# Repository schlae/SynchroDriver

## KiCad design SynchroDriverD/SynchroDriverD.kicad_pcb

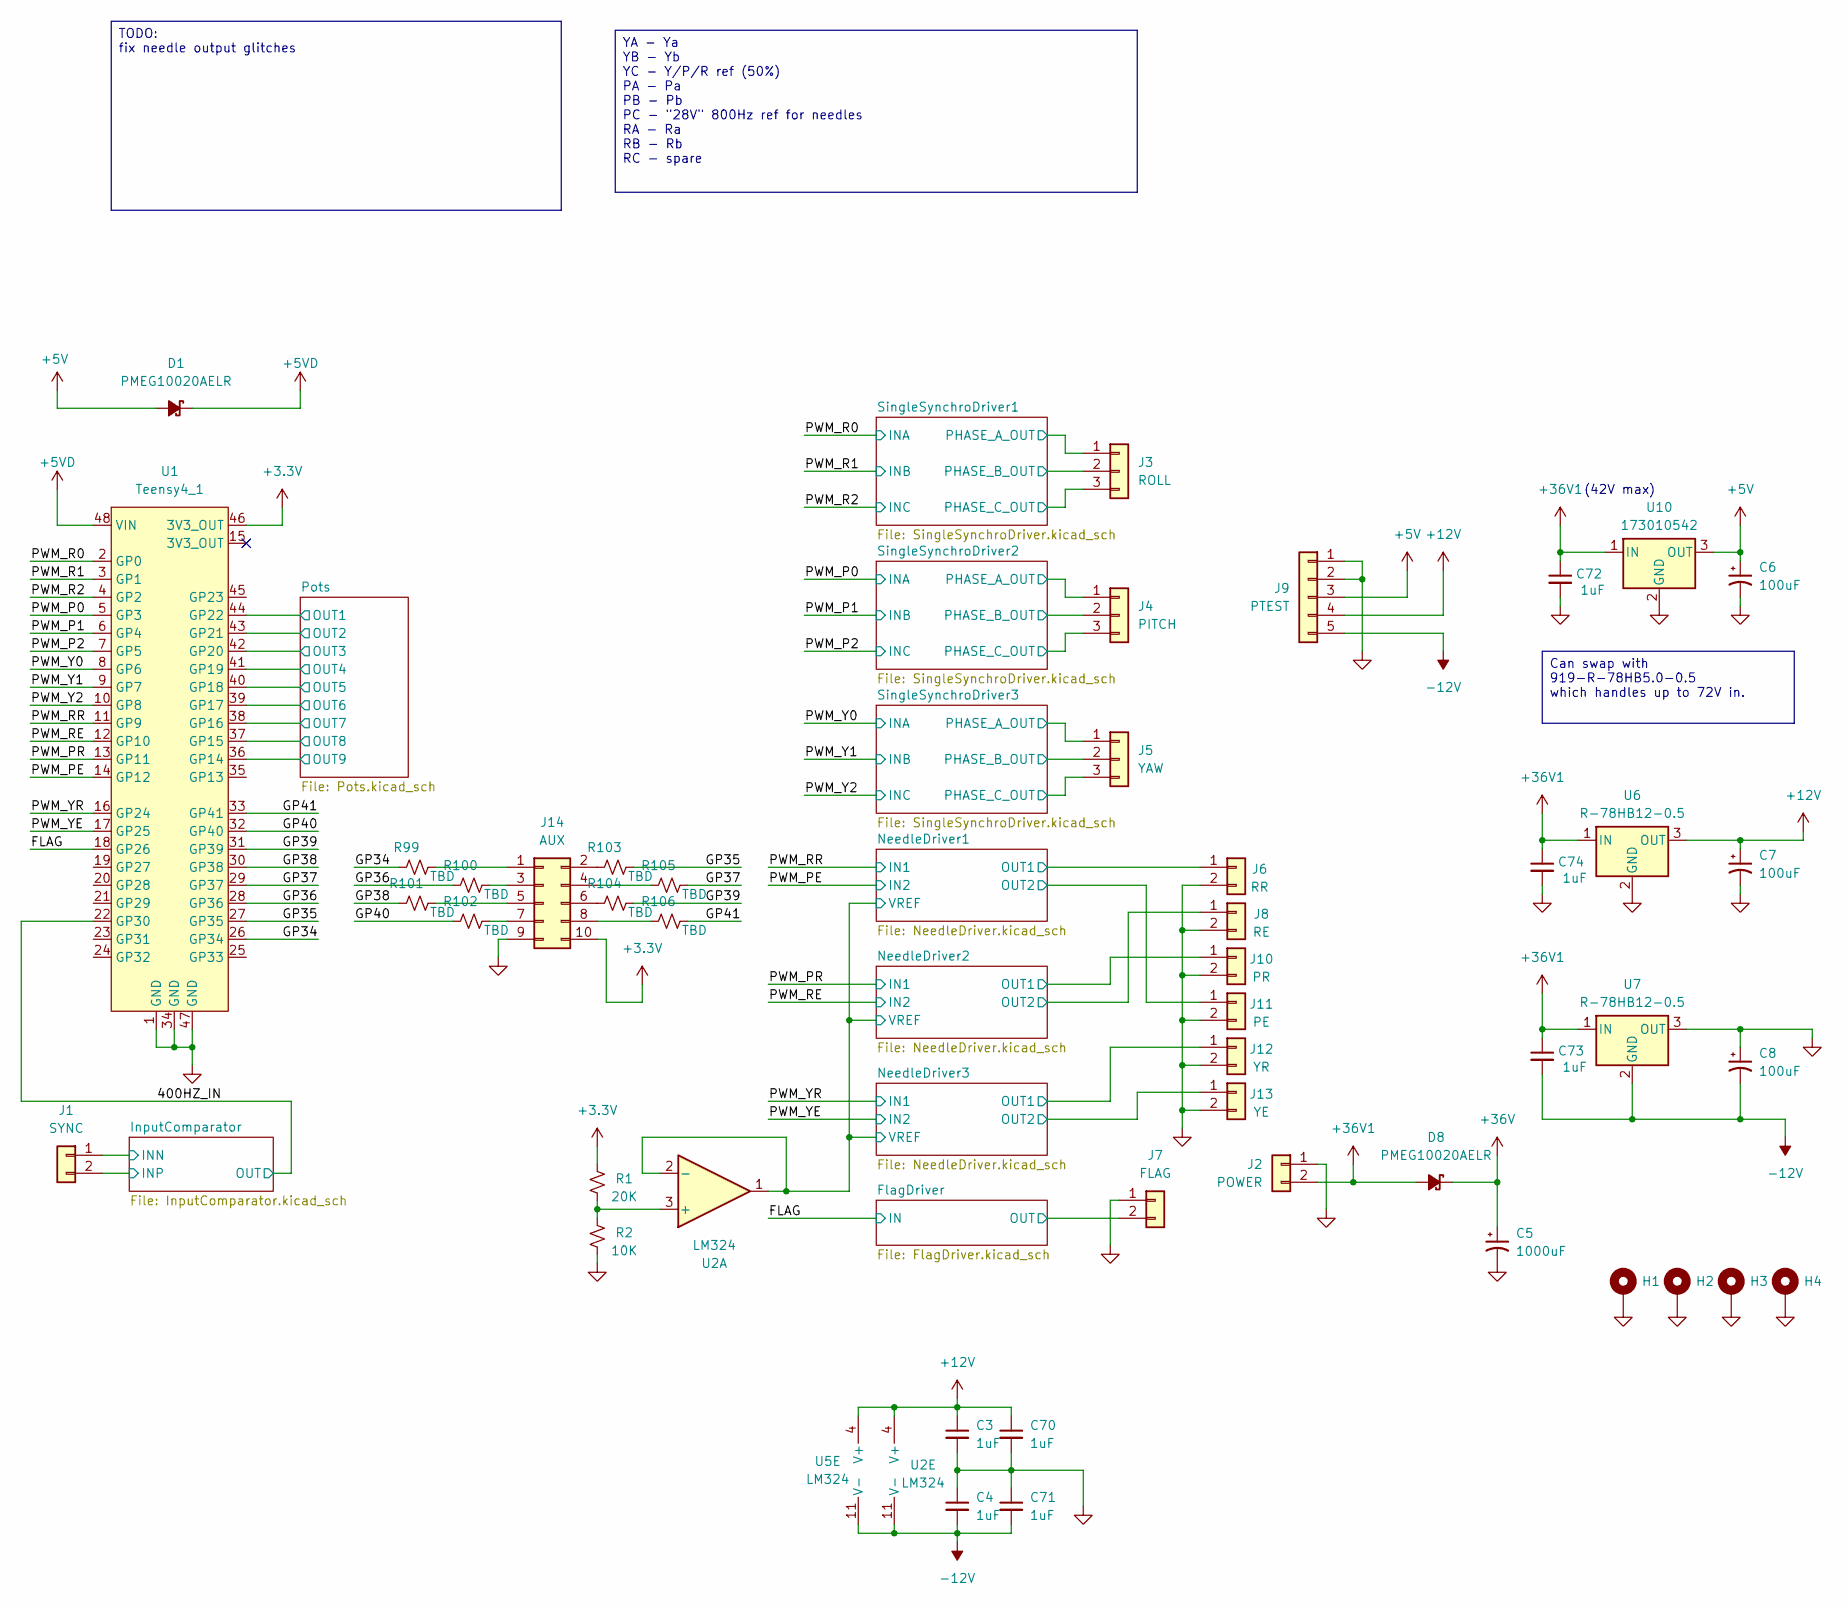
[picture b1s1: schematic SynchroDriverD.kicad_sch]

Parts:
C3, C4, C70, C71: 1uF; CAPC2012X55
C5: 1000uF; CAPAE500P1000X1500
C6, C7, C8: 100uF; CAPAE350P800X700
C72, C73, C74: 1uF; C_1206_3216Metric; MPN CL31A106KBHNNNE
D1, D8: PMEG10020AELR; SOD3716X117; Mouser 771-PMEG10020AELRX
H1, H2, H3, H4: MountingHole_Pad; MountingHole_3.2mm_M3_DIN965_Pad
J1: SYNC; PinHeader_1x02_P2.54mm_Vertical
J2: POWER; TE_826576-2_1x02_P3.96mm_Vertical
J3: ROLL; PinHeader_1x03_P2.54mm_Vertical
J4: PITCH; PinHeader_1x03_P2.54mm_Vertical
J5: YAW; PinHeader_1x03_P2.54mm_Vertical
J6: RR; PinHeader_1x02_P2.54mm_Vertical
J7: FLAG; PinHeader_1x02_P2.54mm_Vertical
J8: RE; PinHeader_1x02_P2.54mm_Vertical
J9: PTEST; TE_826576-5_1x05_P3.96mm_Vertical
J10: PR; PinHeader_1x02_P2.54mm_Vertical
J11: PE; PinHeader_1x02_P2.54mm_Vertical
J12: YR; PinHeader_1x02_P2.54mm_Vertical
J13: YE; PinHeader_1x02_P2.54mm_Vertical
J14: AUX; PinHeader_2x05_P2.54mm_Vertical
R1: 20K; RESC1608X55
R2: 10K; RESC1608X55
R99, R100, R101, R102, R103, R104, R105, R106: TBD; RESC1608X55
U1: Teensy4_1; DIP-48_W15.24mm_Socket
U2, U5: LM324; SOP127P620X175-14; Mouser 863-LM324DR2G
U6, U7: R-78HB12-0.5; DCDC_3PIN_GENERIC_SHIFTED; Mouser 919-R-78HB12-0.5
U10: 173010542; DCDC_3PIN_GENERIC; Mouser 710-173010542

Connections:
+3.3V: J14.10, R1.2, U1.46 (3V3_OUT); also elsewhere on the board
+5V: C6.1, D1.2 (A), J9.3, U10.3 (OUT); also elsewhere on the board
+5VD: D1.1 (K), U1.48 (VIN)
+12V: C3.1, C7.1, C70.1, J9.4, U2.4 (V+), U5.4 (V+), U6.3 (OUT); also elsewhere on the board
+36V: C5.1, D8.1 (K); also elsewhere on the board
+36V1: C72.1, C73.1, C74.1, D8.2 (A), J2.2, U6.1 (IN), U7.1 (IN), U10.1 (IN); also elsewhere on the board
-12V: C4.2, C8.2, C71.2, C73.2, J9.5, U2.11 (V-), U5.11 (V-), U7.2 (GND); also elsewhere on the board
/400HZ_IN: U1.22 (GP30); also elsewhere on the board
/FLAG: U1.18 (GP26); also elsewhere on the board
/FlagDriver/OUT: J7.2; also elsewhere on the board
/GP34: R99.2, U1.26 (GP34)
/GP35: R103.1, U1.27 (GP35)
/GP36: R100.2, U1.28 (GP36)
/GP37: R105.1, U1.29 (GP37)
/GP38: R101.2, U1.30 (GP38)
/GP39: R104.1, U1.31 (GP39)
/GP40: R102.2, U1.32 (GP40)
/GP41: R106.1, U1.33 (GP41)
/InputComparator/INN: J1.1; also elsewhere on the board
/InputComparator/INP: J1.2; also elsewhere on the board
/NeedleDriver1/OUT1: J6.1; also elsewhere on the board
/NeedleDriver1/OUT2: J11.1; also elsewhere on the board
/NeedleDriver1/VREF: U2.1, U2.2 (-), U2.10 (+), U2.12 (+), U5.10 (+), U5.12 (+); also elsewhere on the board
/NeedleDriver2/OUT1: J10.1; also elsewhere on the board
/NeedleDriver2/OUT2: J8.1; also elsewhere on the board
/NeedleDriver3/OUT1: J12.1; also elsewhere on the board
/NeedleDriver3/OUT2: J13.1; also elsewhere on the board
/PWM_P0: U1.5 (GP3); also elsewhere on the board
/PWM_P1: U1.6 (GP4); also elsewhere on the board
/PWM_P2: U1.7 (GP5); also elsewhere on the board
/PWM_PE: U1.14 (GP12); also elsewhere on the board
/PWM_PR: U1.13 (GP11); also elsewhere on the board
/PWM_R0: U1.2 (GP0); also elsewhere on the board
/PWM_R1: U1.3 (GP1); also elsewhere on the board
/PWM_R2: U1.4 (GP2); also elsewhere on the board
/PWM_RE: U1.12 (GP10); also elsewhere on the board
/PWM_RR: U1.11 (GP9); also elsewhere on the board
/PWM_Y0: U1.8 (GP6); also elsewhere on the board
/PWM_Y1: U1.9 (GP7); also elsewhere on the board
/PWM_Y2: U1.10 (GP8); also elsewhere on the board
/PWM_YE: U1.17 (GP25); also elsewhere on the board
/PWM_YR: U1.16 (GP24); also elsewhere on the board
/Pots/OUT1: U1.44 (GP22); also elsewhere on the board
/Pots/OUT2: U1.43 (GP21); also elsewhere on the board
/Pots/OUT3: U1.42 (GP20); also elsewhere on the board
/Pots/OUT4: U1.41 (GP19); also elsewhere on the board
/Pots/OUT5: U1.40 (GP18); also elsewhere on the board
/Pots/OUT6: U1.39 (GP17); also elsewhere on the board
/Pots/OUT7: U1.38 (GP16); also elsewhere on the board
/Pots/OUT8: U1.37 (GP15); also elsewhere on the board
/Pots/OUT9: U1.36 (GP14); also elsewhere on the board
/SingleSynchroDriver1/PHASE_A_OUT: J3.1; also elsewhere on the board
/SingleSynchroDriver1/PHASE_B_OUT: J3.2; also elsewhere on the board
/SingleSynchroDriver1/PHASE_C_OUT: J3.3; also elsewhere on the board
/SingleSynchroDriver2/PHASE_A_OUT: J4.1; also elsewhere on the board
/SingleSynchroDriver2/PHASE_B_OUT: J4.2; also elsewhere on the board
/SingleSynchroDriver2/PHASE_C_OUT: J4.3; also elsewhere on the board
/SingleSynchroDriver3/PHASE_A_OUT: J5.1; also elsewhere on the board
/SingleSynchroDriver3/PHASE_B_OUT: J5.2; also elsewhere on the board
/SingleSynchroDriver3/PHASE_C_OUT: J5.3; also elsewhere on the board
GND: C3.2, C4.1, C5.2, C6.2, C7.2, C8.1, C70.2, C71.1, C72.2, C74.2, H1.1, H2.1, H3.1, H4.1, J2.1, J6.2, J7.1, J8.2, J9.1, J9.2, J10.2, J11.2, J12.2, J13.2, J14.9, R2.1, U1.1 (GND), U1.34 (GND), U1.47 (GND), U6.2 (GND), U7.3 (OUT), U10.2 (GND); also elsewhere on the board
unnamed 77: U5.8; also elsewhere on the board
unnamed 78: U5.14; also elsewhere on the board
unnamed 81: U2.14; also elsewhere on the board
unnamed 82: U2.8; also elsewhere on the board
unnamed: J14.1, R99.1
unnamed: J14.2, R103.2
unnamed: J14.3, R100.1
unnamed: J14.4, R105.2
unnamed: J14.5, R101.1
unnamed: J14.6, R104.2
unnamed: J14.7, R102.1
unnamed: J14.8, R106.2
unnamed: R1.1, R2.2, U2.3 (+)
unnamed 140: U2.9 (-); also elsewhere on the board
unnamed 141: U2.13 (-); also elsewhere on the board
unnamed 144: U5.9 (-); also elsewhere on the board
unnamed 145: U5.13 (-); also elsewhere on the board

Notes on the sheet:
(42V max)
Can swap with 919-R-78HB5.0-0.5 which handles up to 72V in.
YA - Ya YB - Yb YC - Y/P/R ref (50%) PA - Pa PB - Pb PC - "28V" 800Hz ref for needles RA - Ra RB - Rb RC - spare
TODO: fix needle output glitches

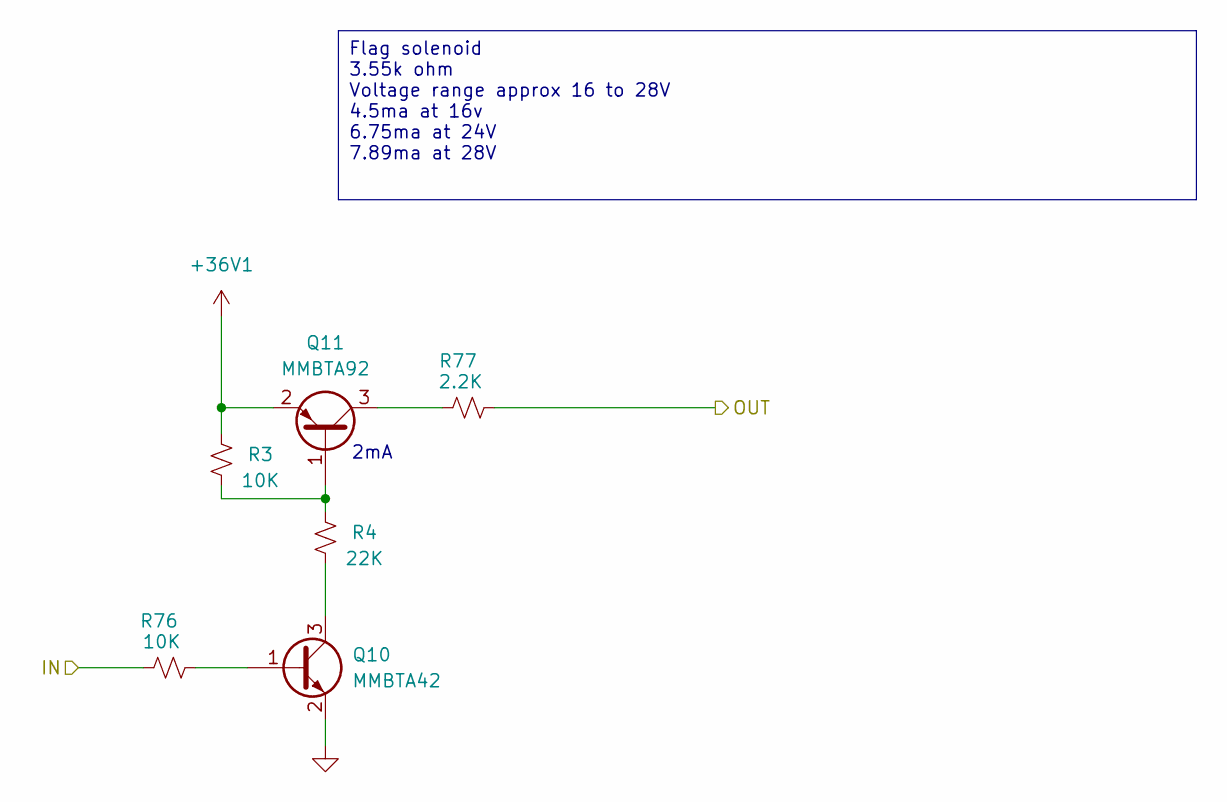
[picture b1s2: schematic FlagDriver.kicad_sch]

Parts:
Q10: MMBTA42; SOT-23; Mouser 637-MMBTA42
Q11: MMBTA92; SOT-23; Mouser 637-MMBTA92
R3, R76: 10K; R_0603_1608Metric
R4: 22K; R_0603_1608Metric
R77: 2.2K; R_0603_1608Metric

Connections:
+36V1: Q11.2 (E), R3.2; also elsewhere on the board
/FLAG: R76.2; also elsewhere on the board
/FlagDriver/OUT: R77.1; also elsewhere on the board
GND: Q10.2 (E); also elsewhere on the board
unnamed: Q10.1 (B), R76.1
unnamed: Q10.3 (C), R4.1
unnamed: Q11.1 (B), R3.1, R4.2
unnamed: Q11.3 (C), R77.2

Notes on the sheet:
2mA
Flag solenoid 3.55k ohm Voltage range approx 16 to 28V 4.5ma at 16v 6.75ma at 24V 7.89ma at 28V

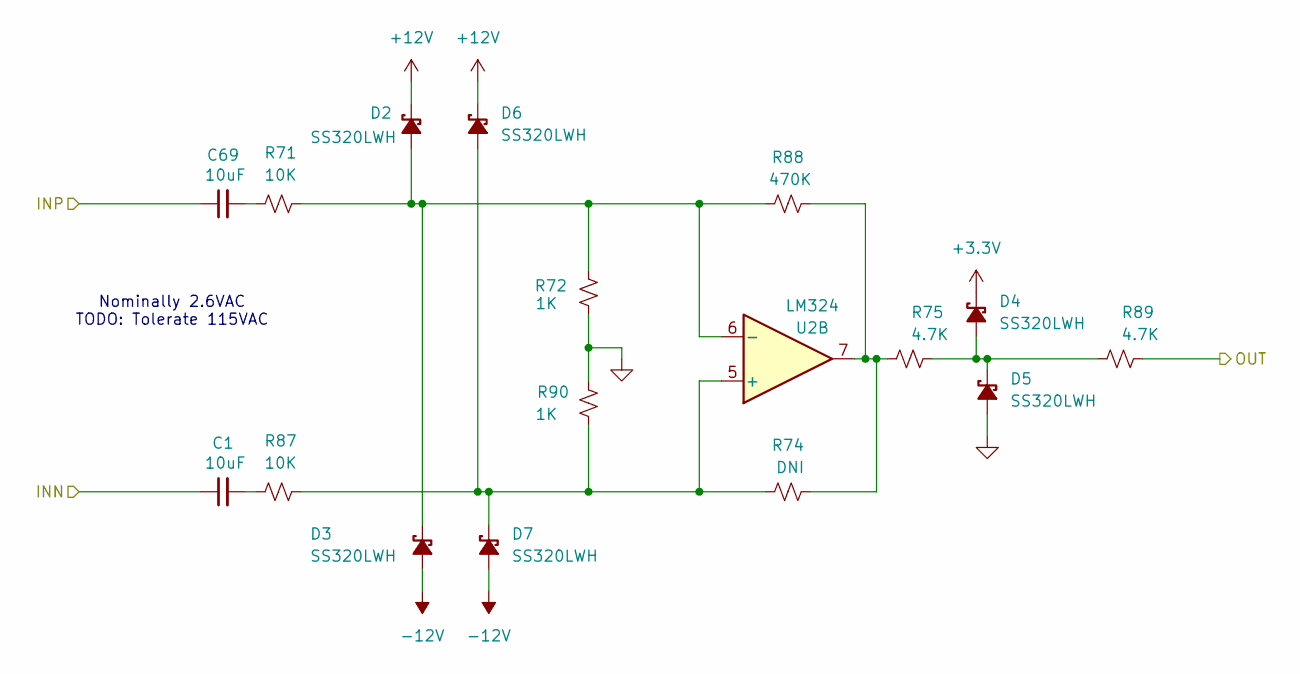
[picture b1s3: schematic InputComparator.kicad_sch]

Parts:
C1, C69: 10uF; C_1206_3216Metric; MPN CL31A106KBHNNNE; Mouser 187-CL31A106KBHNNNE
D2, D3, D4, D5, D6, D7: SS320LWH; SOD3716X117; Mouser 821-SS320LWH
R71, R87: 10K; RESC3216X70
R72, R90: 1K; RESC1608X55
R74: DNI; RESC1608X55
R75, R89: 4.7K; RESC1608X55
R88: 470K; RESC1608X55
U2: LM324; SOP127P620X175-14; Mouser 863-LM324DR2G

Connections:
+3.3V: D4.1 (K); also elsewhere on the board
+12V: D2.1 (K), D6.1 (K); also elsewhere on the board
-12V: D3.2 (A), D7.2 (A); also elsewhere on the board
/400HZ_IN: R89.1; also elsewhere on the board
/InputComparator/INN: C1.1; also elsewhere on the board
/InputComparator/INP: C69.1; also elsewhere on the board
/NeedleDriver1/VREF: U2.10 (+), U2.12 (+); also elsewhere on the board
GND: D5.2 (A), R72.2, R90.1; also elsewhere on the board
unnamed: C1.2, R87.1
unnamed 81: U2.14; also elsewhere on the board
unnamed 82: U2.8; also elsewhere on the board
unnamed: C69.2, R71.1
unnamed: D2.2 (A), D3.1 (K), R71.2, R72.1, R88.2, U2.6 (-)
unnamed: D4.2 (A), D5.1 (K), R75.1, R89.2
unnamed: D6.2 (A), D7.1 (K), R74.2, R87.2, R90.2, U2.5 (+)
unnamed: R74.1, R75.2, R88.1, U2.7
unnamed 140: U2.9 (-); also elsewhere on the board
unnamed 141: U2.13 (-); also elsewhere on the board

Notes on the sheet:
Nominally 2.6VAC TODO: Tolerate 115VAC

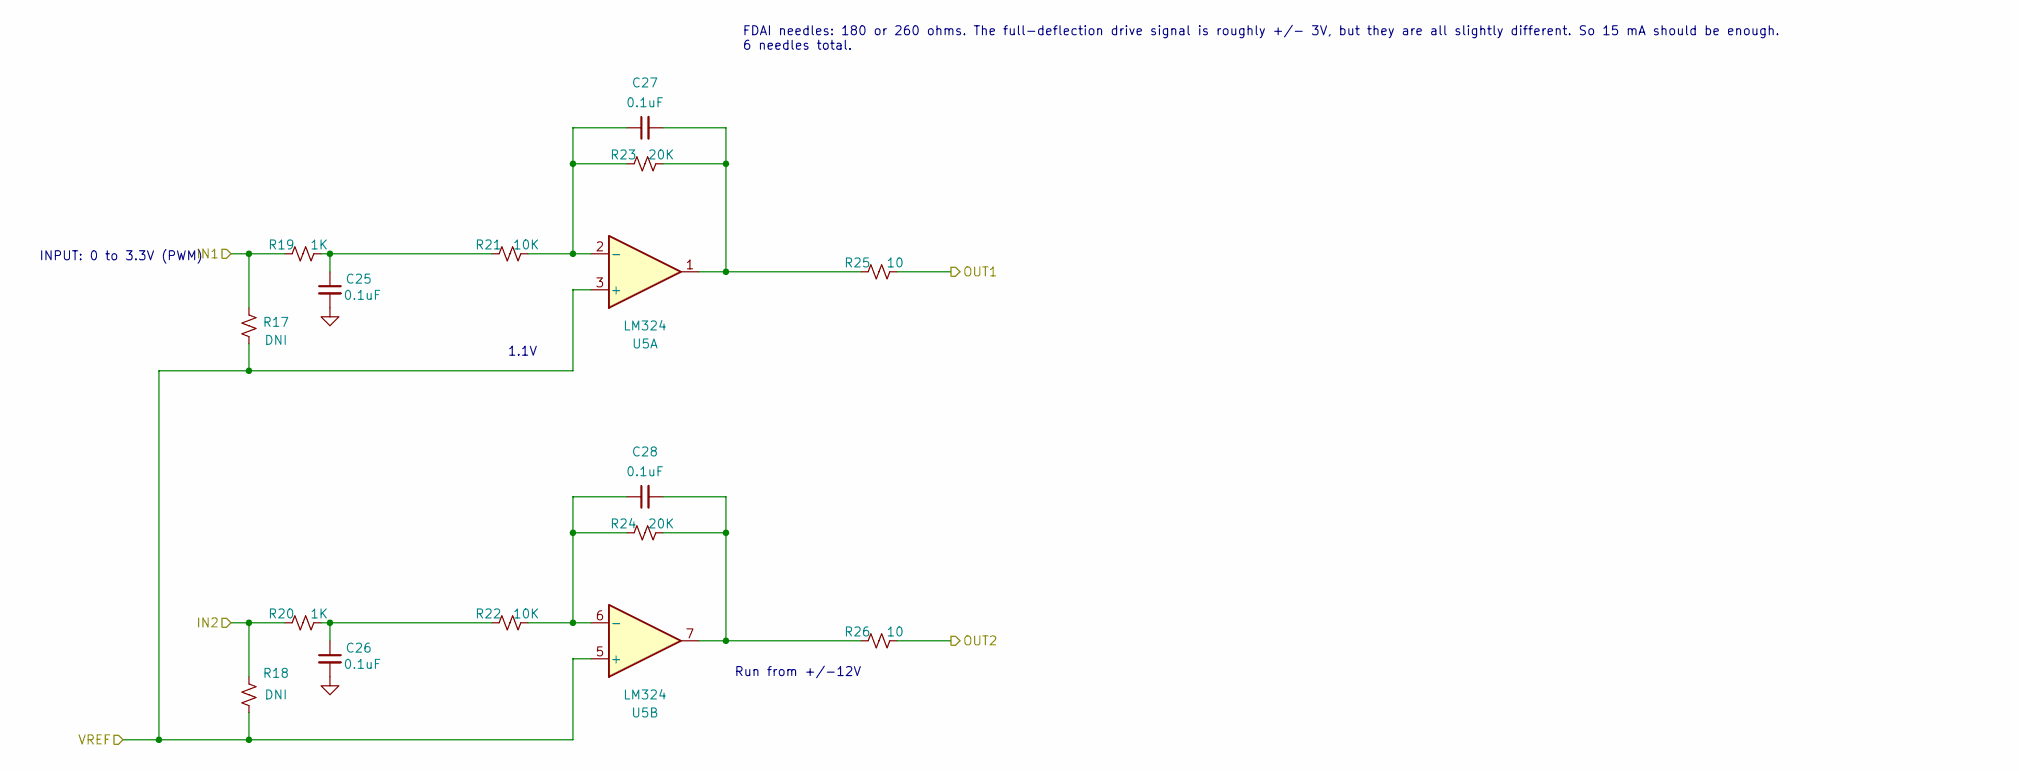
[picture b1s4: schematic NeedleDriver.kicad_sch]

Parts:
C25, C26, C27, C28: 0.1uF; CAPC1608X100
R17, R18: DNI; RESC1608X55
R19, R20: 1K; RESC1608X55
R21, R22: 10K; RESC1608X55
R23, R24: 20K; RESC1608X55
R25, R26: 10; RESC1608X55
U5: LM324; SOP127P620X175-14; Mouser 863-LM324DR2G

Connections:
/NeedleDriver1/OUT1: R25.2; also elsewhere on the board
/NeedleDriver1/OUT2: R26.2; also elsewhere on the board
/NeedleDriver1/VREF: R17.1, R18.1, U5.3 (+), U5.5 (+), U5.10 (+), U5.12 (+); also elsewhere on the board
/PWM_PE: R18.2, R20.1; also elsewhere on the board
/PWM_RR: R17.2, R19.1; also elsewhere on the board
GND: C25.2, C26.2; also elsewhere on the board
unnamed: C25.1, R19.2, R21.1
unnamed: C26.1, R20.2, R22.1
unnamed: C27.2, R23.2, R25.1, U5.1
unnamed: C28.2, R24.2, R26.1, U5.7
unnamed 77: U5.8; also elsewhere on the board
unnamed 78: U5.14; also elsewhere on the board
unnamed: C27.1, R21.2, R23.1, U5.2 (-)
unnamed: C28.1, R22.2, R24.1, U5.6 (-)
unnamed 144: U5.9 (-); also elsewhere on the board
unnamed 145: U5.13 (-); also elsewhere on the board

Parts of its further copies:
C29, C30, C31, C32, C33, C34, C35, C36: 0.1uF; CAPC1608X100
R27, R28, R37, R38: DNI; RESC1608X55
R29, R30, R39, R40: 1K; RESC1608X55
R31, R32, R41, R42: 10K; RESC1608X55
R33, R34, R43, R44: 20K; RESC1608X55
R35, R36, R45, R46: 10; RESC1608X55

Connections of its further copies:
/NeedleDriver1/VREF: R27.1, R28.1, R37.1, R38.1; also elsewhere on the board
/NeedleDriver2/OUT1: R35.2; also elsewhere on the board
/NeedleDriver2/OUT2: R36.2; also elsewhere on the board
/NeedleDriver3/OUT1: R45.2; also elsewhere on the board
/NeedleDriver3/OUT2: R46.2; also elsewhere on the board
/PWM_PR: R27.2, R29.1; also elsewhere on the board
/PWM_RE: R28.2, R30.1; also elsewhere on the board
/PWM_YE: R38.2, R40.1; also elsewhere on the board
/PWM_YR: R37.2, R39.1; also elsewhere on the board
GND: C29.2, C30.2, C33.2, C34.2; also elsewhere on the board
unnamed: C29.1, R29.2, R31.1
unnamed: C30.1, R30.2, R32.1
unnamed 77: C31.2, R33.2, R35.1; also elsewhere on the board
unnamed 78: C32.2, R34.2, R36.1; also elsewhere on the board
unnamed: C33.1, R39.2, R41.1
unnamed: C34.1, R40.2, R42.1
unnamed 81: C35.2, R43.2, R45.1; also elsewhere on the board
unnamed 82: C36.2, R44.2, R46.1; also elsewhere on the board
unnamed 140: C36.1, R42.2, R44.1; also elsewhere on the board
unnamed 141: C35.1, R41.2, R43.1; also elsewhere on the board
unnamed 144: C31.1, R31.2, R33.1; also elsewhere on the board
unnamed 145: C32.1, R32.2, R34.1; also elsewhere on the board

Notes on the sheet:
1.1V
Run from +/-12V
FDAI needles: 180 or 260 ohms. The full-deflection drive signal is roughly +/- 3V, but they are all slightly different. So 15 mA should be enough. 6 needles total.
INPUT: 0 to 3.3V (PWM)

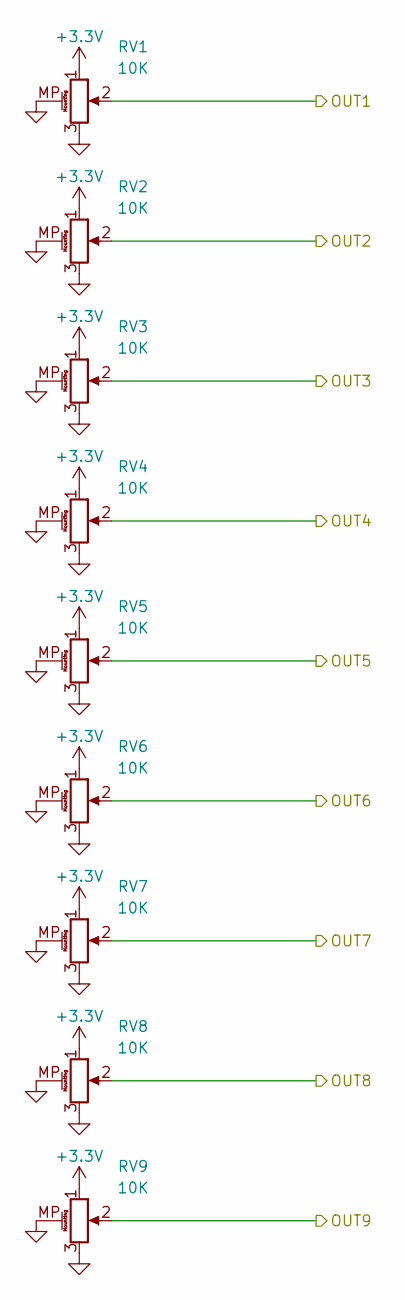
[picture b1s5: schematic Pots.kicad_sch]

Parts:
RV1, RV2, RV3, RV4, RV5, RV6, RV7, RV8, RV9: 10K; BOURNS_PTV09A_H; MPN PTV09A4030FB103; Mouser 652-PTV09A4030FB103

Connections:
+3.3V: RV1.1, RV2.1, RV3.1, RV4.1, RV5.1, RV6.1, RV7.1, RV8.1, RV9.1; also elsewhere on the board
/Pots/OUT1: RV1.2; also elsewhere on the board
/Pots/OUT2: RV2.2; also elsewhere on the board
/Pots/OUT3: RV3.2; also elsewhere on the board
/Pots/OUT4: RV4.2; also elsewhere on the board
/Pots/OUT5: RV5.2; also elsewhere on the board
/Pots/OUT6: RV6.2; also elsewhere on the board
/Pots/OUT7: RV7.2; also elsewhere on the board
/Pots/OUT8: RV8.2; also elsewhere on the board
/Pots/OUT9: RV9.2; also elsewhere on the board
GND: RV1.3, RV1.MP (MountPin), RV2.3, RV2.MP (MountPin), RV3.3, RV3.MP (MountPin), RV4.3, RV4.MP (MountPin), RV5.3, RV5.MP (MountPin), RV6.3, RV6.MP (MountPin), RV7.3, RV7.MP (MountPin), RV8.3, RV8.MP (MountPin), RV9.3, RV9.MP (MountPin); also elsewhere on the board

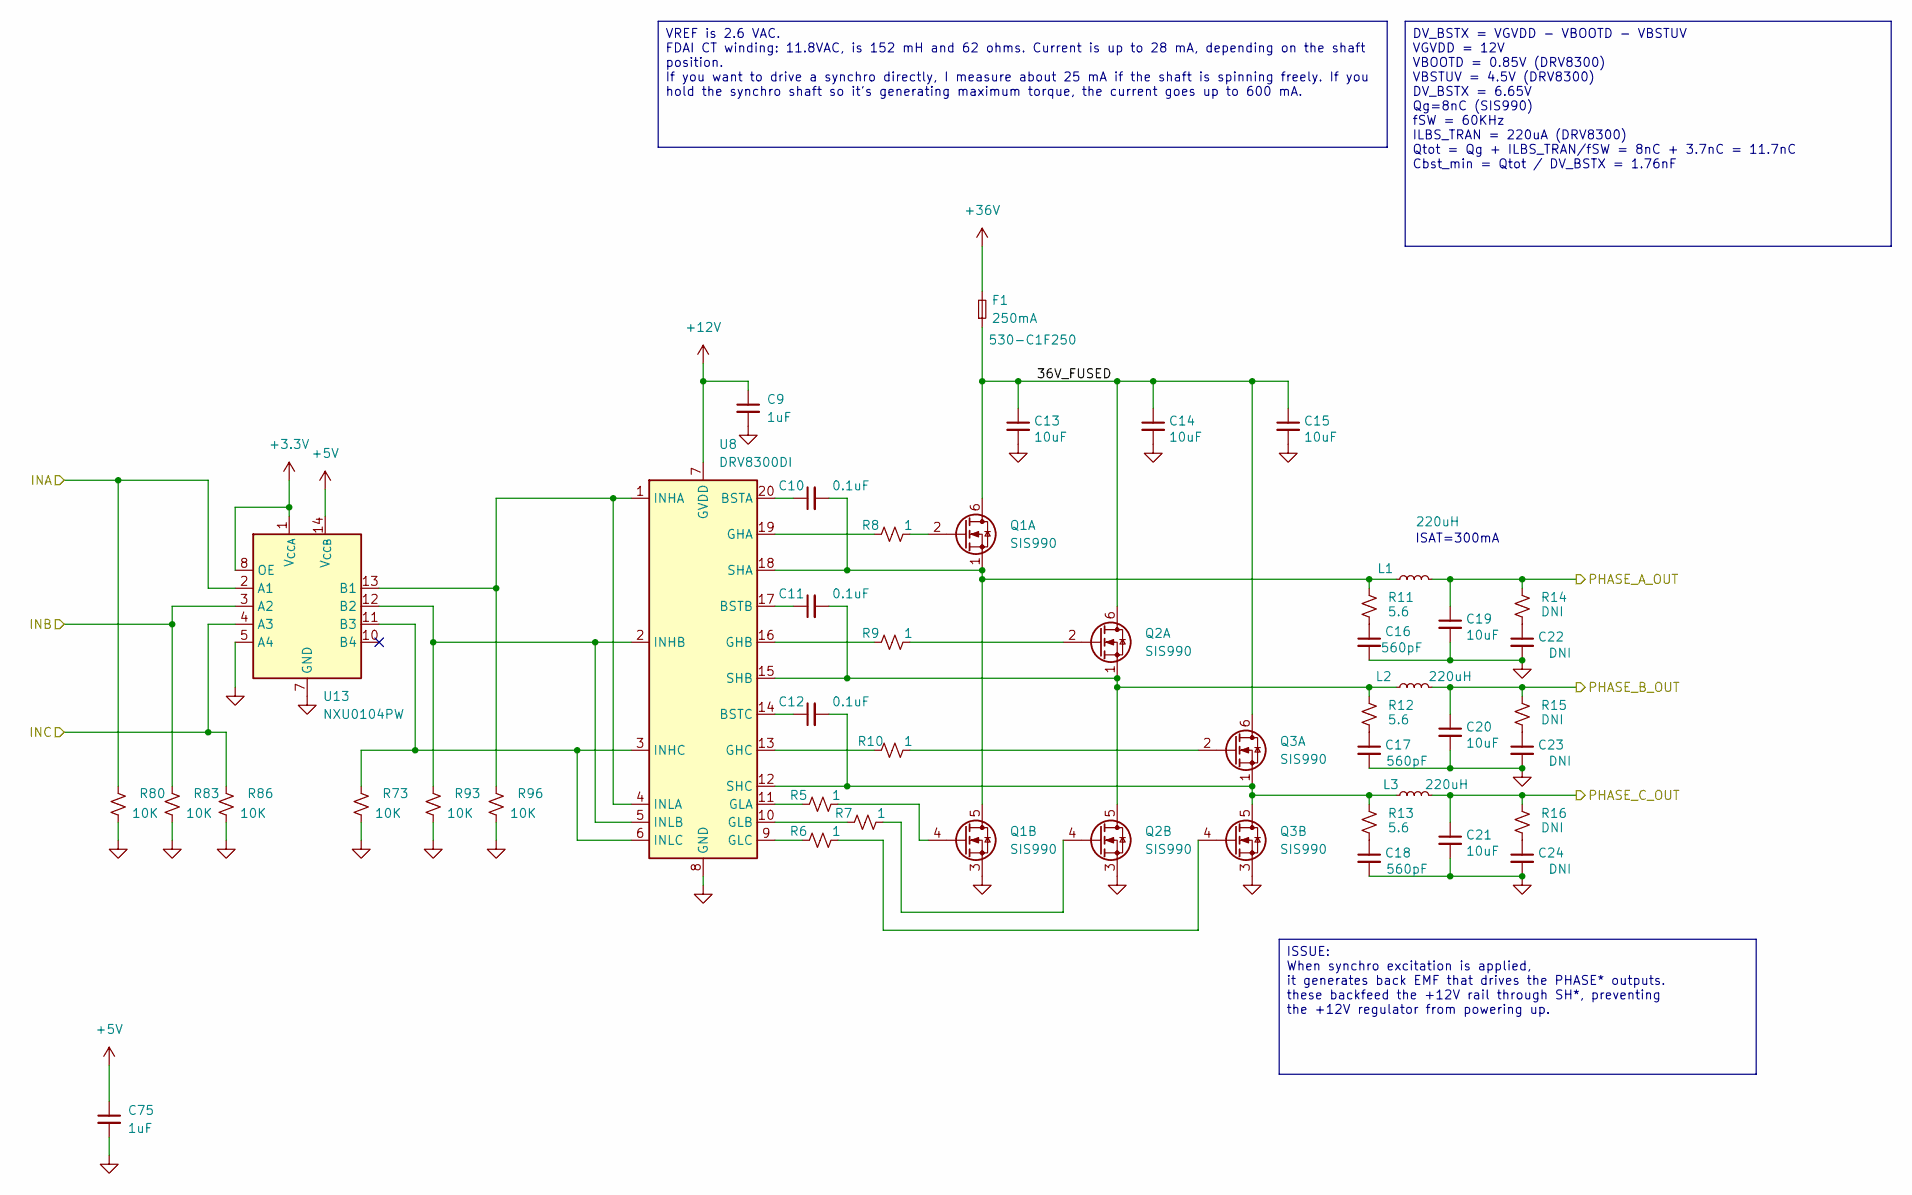
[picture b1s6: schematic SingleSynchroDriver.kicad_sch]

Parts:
C9, C75: 1uF; CAPC2012X55
C10, C11, C12: 0.1uF; CAPC1608X100
C13, C14, C15, C19, C20, C21: 10uF; C_1206_3216Metric; MPN CL31A106KBHNNNE; Mouser 187-CL31A106KBHNNNE
C16, C17, C18: 560pF; CAPC2012X55
C22, C23, C24: DNI; CAPC2012X55
F1: 250mA; Fuse_1206_3216Metric_Pad1.42x1.75mm_HandSolder; Mouser 530-C1F250
L1, L2, L3: 220uH; L_7.3x7.3_H3.5; MPN B82472G4224M000; Mouser 871-B82472G4224M
Q1, Q2, Q3: SIS990; Vishay_PowerPAK_1212-8_Dual; Mouser 78-SIS990DN-T1-GE3
R5, R6, R7, R8, R9, R10: 1; RESC1608X55
R11, R12, R13: 5.6; RESC2012X55
R14, R15, R16: DNI; RESC2012X55
R73, R80, R83, R86, R93, R96: 10K; RESC1608X55
U8: DRV8300DI; TSOP65P640X110-20; Mouser 595-DRV8300DIPWR
U13: NXU0104PW; TSSOP-14_4.4x5mm_P0.65mm

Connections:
+3.3V: U13.1 (V_{CCA}), U13.8 (OE); also elsewhere on the board
+5V: C75.1, U13.14 (V_{CCB}); also elsewhere on the board
+12V: C9.1, U8.7 (GVDD); also elsewhere on the board
+36V: F1.2; also elsewhere on the board
/PWM_R0: R80.2, U13.2 (A1); also elsewhere on the board
/PWM_R1: R83.2, U13.3 (A2); also elsewhere on the board
/PWM_R2: R86.2, U13.4 (A3); also elsewhere on the board
/SingleSynchroDriver1/36V_FUSED: C13.1, C14.1, C15.1, F1.1, Q1.6 (D), Q2.6 (D), Q3.6 (D)
/SingleSynchroDriver1/PHASE_A_OUT: C19.1, L1.2, R14.1; also elsewhere on the board
/SingleSynchroDriver1/PHASE_B_OUT: C20.1, L2.2, R15.1; also elsewhere on the board
/SingleSynchroDriver1/PHASE_C_OUT: C21.1, L3.2, R16.1; also elsewhere on the board
GND: C9.2, C13.2, C14.2, C15.2, C16.2, C17.2, C18.2, C19.2, C20.2, C21.2, C22.2, C23.2, C24.2, C75.2, Q1.3 (S), Q2.3 (S), Q3.3 (S), R73.1, R80.1, R83.1, R86.1, R93.1, R96.1, U8.8 (GND), U13.5 (A4), U13.7 (GND); also elsewhere on the board
unnamed: C16.1, R11.2
unnamed: C17.1, R12.2
unnamed: C18.1, R13.2
unnamed: C22.1, R14.2
unnamed: C23.1, R15.2
unnamed: C24.1, R16.2
unnamed: Q1.2 (G), R8.2
unnamed: C10.2, L1.1, Q1.1 (S), Q1.5 (D), R11.1, U8.18 (SHA)
unnamed: Q1.4 (G), R5.2
unnamed: Q2.2 (G), R9.2
unnamed: C11.2, L2.1, Q2.1 (S), Q2.5 (D), R12.1, U8.15 (SHB)
unnamed: Q2.4 (G), R7.2
unnamed: Q3.2 (G), R10.2
unnamed: C12.2, L3.1, Q3.1 (S), Q3.5 (D), R13.1, U8.12 (SHC)
unnamed: Q3.4 (G), R6.2
unnamed: C10.1, U8.20 (BSTA)
unnamed: C11.1, U8.17 (BSTB)
unnamed: C12.1, U8.14 (BSTC)
unnamed: R8.1, U8.19 (GHA)
unnamed: R9.1, U8.16 (GHB)
unnamed: R10.1, U8.13 (GHC)
unnamed: R5.1, U8.11 (GLA)
unnamed: R7.1, U8.10 (GLB)
unnamed: R6.1, U8.9 (GLC)
unnamed: R96.2, U8.1 (INHA), U8.4 (INLA), U13.13 (B1)
unnamed: R93.2, U8.2 (INHB), U8.5 (INLB), U13.12 (B2)
unnamed: R73.2, U8.3 (INHC), U8.6 (INLC), U13.11 (B3)

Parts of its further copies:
C37, C53, C76, C77: 1uF; CAPC2012X55
C38, C39, C40, C54, C55, C56: 0.1uF; CAPC1608X100
C41, C42, C43, C47, C48, C49, C57, C58, C59, C63, C64, C65: 10uF; C_1206_3216Metric; MPN CL31A106KBHNNNE; Mouser 187-CL31A106KBHNNNE
C44, C45, C46, C60, C61, C62: 560pF; CAPC2012X55
C50, C51, C52, C66, C67, C68: DNI; CAPC2012X55
F2, F3: 250mA; Fuse_1206_3216Metric_Pad1.42x1.75mm_HandSolder; Mouser 530-C1F250
L4, L5, L6, L7, L8, L9: 220uH; L_7.3x7.3_H3.5; MPN B82472G4224M000; Mouser 871-B82472G4224M
Q4, Q5, Q6, Q7, Q8, Q9: SIS990; Vishay_PowerPAK_1212-8_Dual; Mouser 78-SIS990DN-T1-GE3
R47, R48, R49, R50, R51, R52, R59, R60, R61, R62, R63, R64: 1; RESC1608X55
R53, R54, R55, R65, R66, R67: 5.6; RESC2012X55
R56, R57, R58, R68, R69, R70: DNI; RESC2012X55
R78, R79, R81, R82, R84, R85, R91, R92, R94, R95, R97, R98: 10K; RESC1608X55
U9, U11: DRV8300DI; TSOP65P640X110-20; Mouser 595-DRV8300DIPWR
U14, U15: NXU0104PW; TSSOP-14_4.4x5mm_P0.65mm

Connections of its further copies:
+3.3V: U14.1 (V_{CCA}), U14.8 (OE), U15.1 (V_{CCA}), U15.8 (OE); also elsewhere on the board
+5V: C76.1, C77.1, U14.14 (V_{CCB}), U15.14 (V_{CCB}); also elsewhere on the board
+12V: C37.1, C53.1, U9.7 (GVDD), U11.7 (GVDD); also elsewhere on the board
+36V: F2.2, F3.2; also elsewhere on the board
/PWM_P0: R81.2, U14.2 (A1); also elsewhere on the board
/PWM_P1: R84.2, U14.3 (A2); also elsewhere on the board
/PWM_P2: R91.2, U14.4 (A3); also elsewhere on the board
/PWM_Y0: R82.2, U15.2 (A1); also elsewhere on the board
/PWM_Y1: R85.2, U15.3 (A2); also elsewhere on the board
/PWM_Y2: R92.2, U15.4 (A3); also elsewhere on the board
/SingleSynchroDriver2/36V_FUSED: C41.1, C42.1, C43.1, F2.1, Q4.6 (D), Q5.6 (D), Q6.6 (D)
/SingleSynchroDriver2/PHASE_A_OUT: C47.1, L4.2, R56.1; also elsewhere on the board
/SingleSynchroDriver2/PHASE_B_OUT: C48.1, L5.2, R57.1; also elsewhere on the board
/SingleSynchroDriver2/PHASE_C_OUT: C49.1, L6.2, R58.1; also elsewhere on the board
/SingleSynchroDriver3/36V_FUSED: C57.1, C58.1, C59.1, F3.1, Q7.6 (D), Q8.6 (D), Q9.6 (D)
/SingleSynchroDriver3/PHASE_A_OUT: C63.1, L7.2, R68.1; also elsewhere on the board
/SingleSynchroDriver3/PHASE_B_OUT: C64.1, L8.2, R69.1; also elsewhere on the board
/SingleSynchroDriver3/PHASE_C_OUT: C65.1, L9.2, R70.1; also elsewhere on the board
GND: C37.2, C41.2, C42.2, C43.2, C44.2, C45.2, C46.2, C47.2, C48.2, C49.2, C50.2, C51.2, C52.2, C53.2, C57.2, C58.2, C59.2, C60.2, C61.2, C62.2, C63.2, C64.2, C65.2, C66.2, C67.2, C68.2, C76.2, C77.2, Q4.3 (S), Q5.3 (S), Q6.3 (S), Q7.3 (S), Q8.3 (S), Q9.3 (S), R78.1, R79.1, R81.1, R82.1, R84.1, R85.1, R91.1, R92.1, R94.1, R95.1, R97.1, R98.1, U9.8 (GND), U11.8 (GND), U14.5 (A4), U14.7 (GND), U15.5 (A4), U15.7 (GND); also elsewhere on the board
unnamed: C44.1, R53.2
unnamed: C45.1, R54.2
unnamed: C46.1, R55.2
unnamed: C50.1, R56.2
unnamed: C51.1, R57.2
unnamed: C52.1, R58.2
unnamed: C60.1, R65.2
unnamed: C61.1, R66.2
unnamed: C62.1, R67.2
unnamed: C66.1, R68.2
unnamed: C67.1, R69.2
unnamed: C68.1, R70.2
unnamed: Q4.2 (G), R50.2
unnamed: C38.2, L4.1, Q4.1 (S), Q4.5 (D), R53.1, U9.18 (SHA)
unnamed: Q4.4 (G), R47.2
unnamed: Q5.2 (G), R51.2
unnamed: C39.2, L5.1, Q5.1 (S), Q5.5 (D), R54.1, U9.15 (SHB)
unnamed: Q5.4 (G), R49.2
unnamed: Q6.2 (G), R52.2
unnamed: C40.2, L6.1, Q6.1 (S), Q6.5 (D), R55.1, U9.12 (SHC)
unnamed: Q6.4 (G), R48.2
unnamed: Q7.2 (G), R62.2
unnamed: C54.2, L7.1, Q7.1 (S), Q7.5 (D), R65.1, U11.18 (SHA)
unnamed: Q7.4 (G), R59.2
unnamed: Q8.2 (G), R63.2
unnamed: C55.2, L8.1, Q8.1 (S), Q8.5 (D), R66.1, U11.15 (SHB)
unnamed: Q8.4 (G), R61.2
unnamed: Q9.2 (G), R64.2
unnamed: C56.2, L9.1, Q9.1 (S), Q9.5 (D), R67.1, U11.12 (SHC)
unnamed: Q9.4 (G), R60.2
unnamed: C38.1, U9.20 (BSTA)
unnamed: C39.1, U9.17 (BSTB)
unnamed: C40.1, U9.14 (BSTC)
unnamed: R50.1, U9.19 (GHA)
unnamed: R51.1, U9.16 (GHB)
unnamed: R52.1, U9.13 (GHC)
unnamed: R47.1, U9.11 (GLA)
unnamed: R49.1, U9.10 (GLB)
unnamed: R48.1, U9.9 (GLC)
unnamed: C54.1, U11.20 (BSTA)
unnamed: C55.1, U11.17 (BSTB)
unnamed: C56.1, U11.14 (BSTC)
unnamed: R62.1, U11.19 (GHA)
unnamed: R63.1, U11.16 (GHB)
unnamed: R64.1, U11.13 (GHC)
unnamed: R59.1, U11.11 (GLA)
unnamed: R61.1, U11.10 (GLB)
unnamed: R60.1, U11.9 (GLC)
unnamed: R98.2, U11.1 (INHA), U11.4 (INLA), U15.13 (B1)
unnamed: R95.2, U11.2 (INHB), U11.5 (INLB), U15.12 (B2)
unnamed: R79.2, U11.3 (INHC), U11.6 (INLC), U15.11 (B3)
unnamed: R97.2, U9.1 (INHA), U9.4 (INLA), U14.13 (B1)
unnamed: R94.2, U9.2 (INHB), U9.5 (INLB), U14.12 (B2)
unnamed: R78.2, U9.3 (INHC), U9.6 (INLC), U14.11 (B3)

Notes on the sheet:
ISAT=300mA
DV_BSTX = VGVDD - VBOOTD - VBSTUV VGVDD = 12V VBOOTD = 0.85V (DRV8300) VBSTUV = 4.5V (DRV8300) DV_BSTX = 6.65V Qg=8nC (SIS990) fSW = 60KHz ILBS_TRAN = 220uA (DRV8300) Qtot = Qg + ILBS_TRAN/fSW = 8nC + 3.7nC = 11.7nC Cbst_min = Qtot / DV_BSTX = 1.76nF
VREF is 2.6 VAC. FDAI CT winding: 11.8VAC, is 152 mH and 62 ohms. Current is up to 28 mA, depending on the shaft position. If you want to drive a synchro directly, I measure about 25 mA if the shaft is spinning freely. If you hold the synchro shaft so it's generating maximum torque, the current goe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
ISSUE: When synchro excitation is applied, it generates back EMF that drives the PHASE* outputs. these backfeed the +12V rail through SH*, preventing the +12V regulator from powering up.

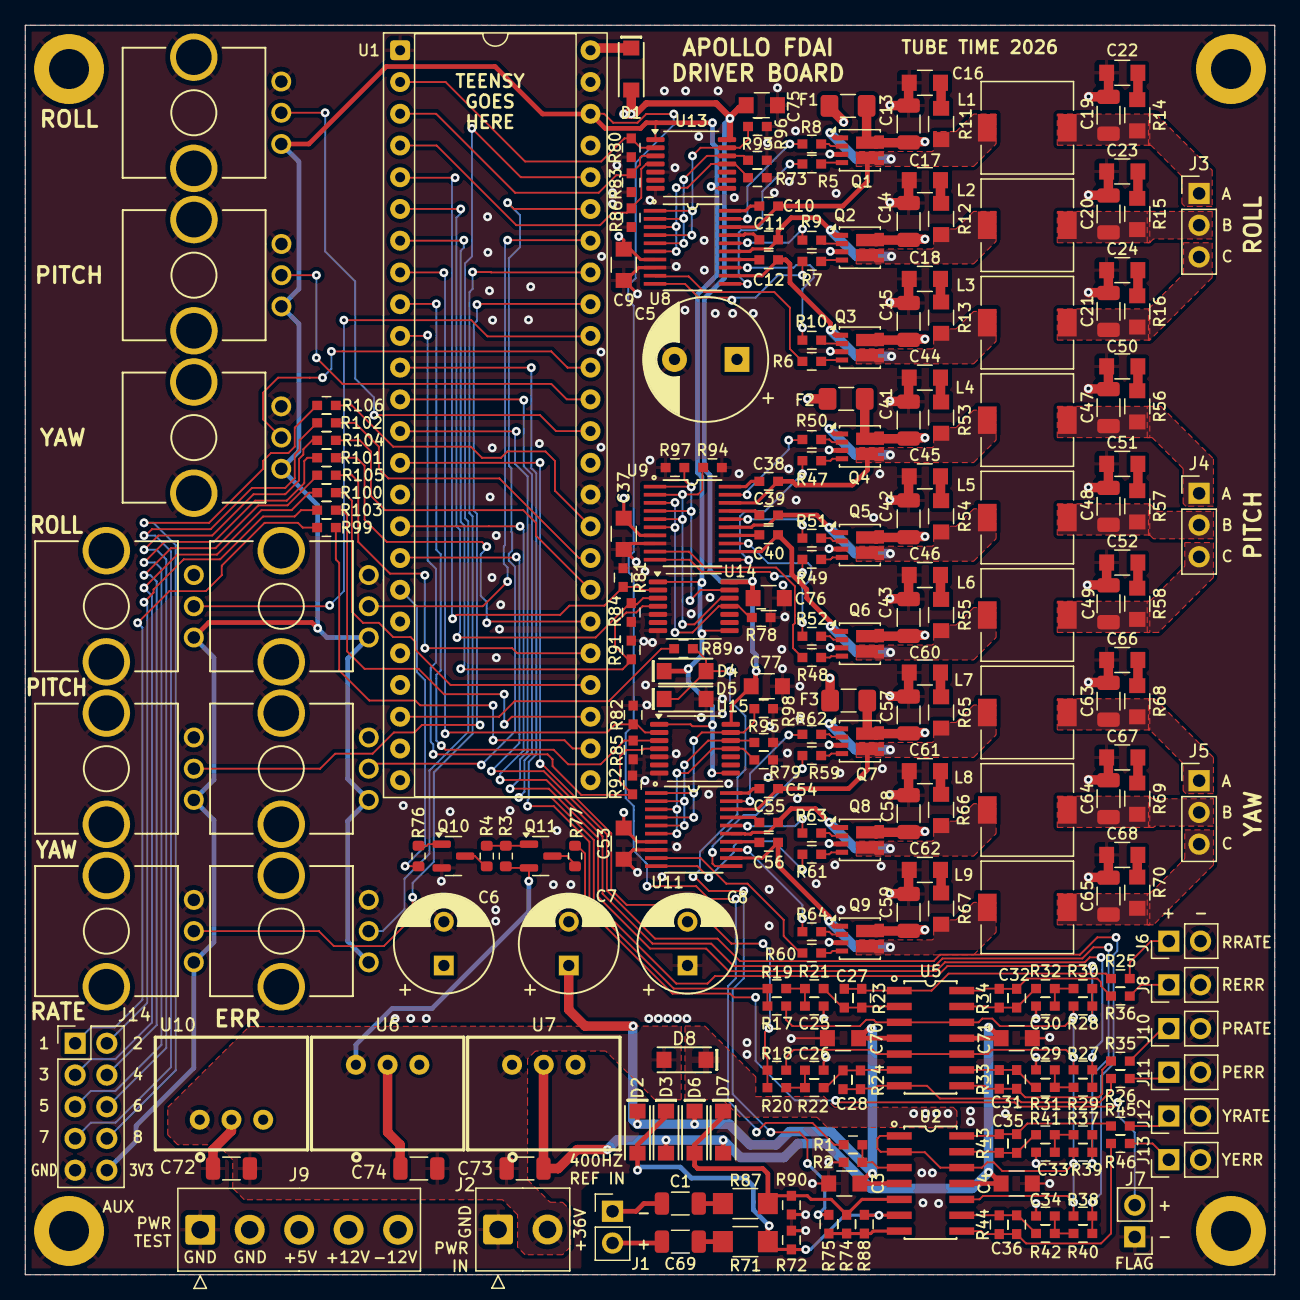
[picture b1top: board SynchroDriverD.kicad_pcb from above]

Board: 2 copper layers, 100.0 x 100.0 mm, 252 parts (0 on the bottom side), 182 nets.

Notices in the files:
SynchroDriverAS/SynchroDriverAS.kicad_pcb:
©2025 TUBE TIME
